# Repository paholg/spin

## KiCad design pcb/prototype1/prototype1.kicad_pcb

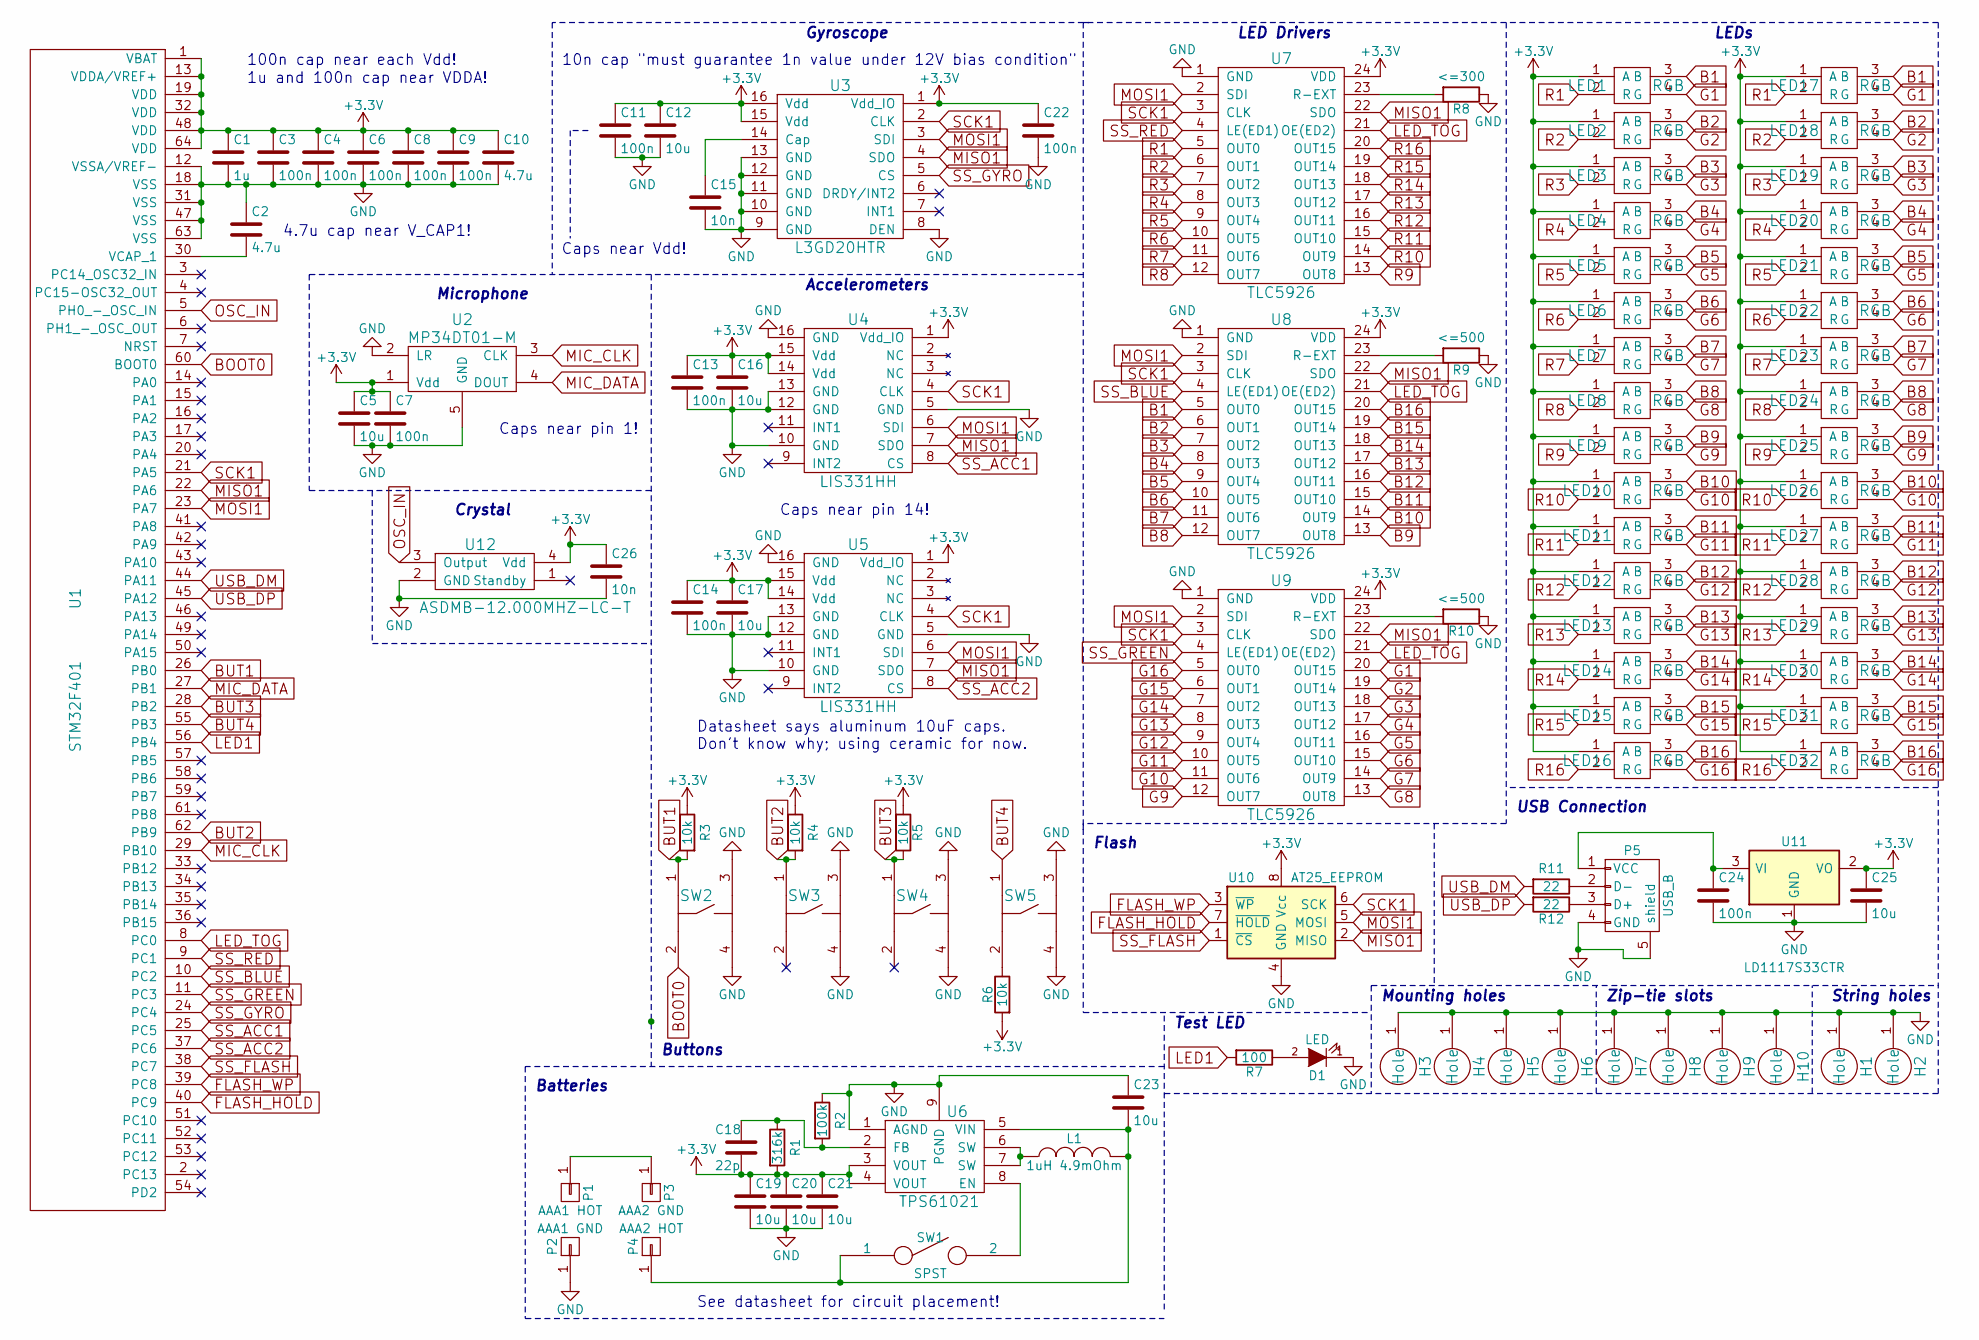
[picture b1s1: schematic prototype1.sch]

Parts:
C1: 1u; C_0805_HandSoldering
C2, C10: 4.7u; C_0603_HandSoldering
C3, C4, C6, C7, C8, C9, C11, C13, C14, C22, C24: 100n; C_0603_HandSoldering
C5, C12, C16, C17, C19, C20, C21, C23, C25: 10u; C_0805_HandSoldering
C15, C26: 10n; C_0805_HandSoldering
C18: 22p; C_0805_HandSoldering
D1: LED; LED_0603
H1, H2, H3, H4, H5, H6: Hole; Hole-3mm
H7, H8, H9, H10: Hole; Zip-tie-slot
L1: 1uH 4.9mOhm; SRU1028-10x10-Octogon
LED1, LED2, LED3, LED4, LED5, LED6, LED7, LED8, LED9, LED10, LED11, LED12, LED13, LED14, LED15, LED16, LED17, LED18, LED19, LED20, LED21, LED22, LED23, LED24, LED25, LED26, LED27, LED28, LED29, LED30, LED31, LED32: RGB; LED_CLV1L-PLCC4
P1: AAA1 HOT; test_pin
P2: AAA1 GND; test_pin
P3: AAA2 GND; test_pin
P4: AAA2 HOT; test_pin
P5: USB_B; ZX62M-B-5P
R1: 316k; R_1206_HandSoldering
R2: 100k; R_0805_HandSoldering
R3, R4, R5, R6: 10k; R_0805_HandSoldering
R7: 100; R_0805_HandSoldering
R8: <=300; Resistor_Vertical_RM5mm
R9, R10: <=500; Resistor_Vertical_RM5mm
R11, R12: 22; R_0603_HandSoldering
SW1: SPST; EVP-AYG0BA
SW2, SW3, SW4, SW5: SPST_two_terminals; Button
U1: STM32F401; TQFP-64_10x10mm_Pitch0.5mm
U2: MP34DT01-M
U3: L3GD20HTR; LGA16
U4, U5: LIS331HH; LGA16
U6: TPS61021; WSON-8_2x2mm
U7, U8, U9: TLC5926
U10: AT25_EEPROM; SOIC-8_3.9x4.9mm_Pitch1.27mm
U11: LD1117S33CTR; SOT-223
U12: ASDMB-12.000MHZ-LC-T

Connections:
+3V3: C1.1, C3.1, C4.1, C5.1, C6.1, C7.1, C8.1, C9.1, C10.1, C11.1, C12.1, C13.1, C14.1, C16.1, C17.1, C18.2, C19.1, C20.1, C21.1, C22.1, C25.1, C26.1, LED1.1 (A), LED2.1 (A), LED3.1 (A), LED4.1 (A), LED5.1 (A), LED6.1 (A), LED7.1 (A), LED8.1 (A), LED9.1 (A), LED10.1 (A), LED11.1 (A), LED12.1 (A), LED13.1 (A), LED14.1 (A), LED15.1 (A), LED16.1 (A), LED17.1 (A), LED18.1 (A), LED19.1 (A), LED20.1 (A), LED21.1 (A), LED22.1 (A), LED23.1 (A), LED24.1 (A), LED25.1 (A), LED26.1 (A), LED27.1 (A), LED28.1 (A), LED29.1 (A), LED30.1 (A), LED31.1 (A), LED32.1 (A), R1.2, R3.1, R4.1, R5.2, R6.2, U1.1 (VBAT), U1.13 (VDDA/VREF+), U1.19 (VDD), U1.32 (VDD), U1.48 (VDD), U1.64 (VDD), U2.1 (Vdd), U3.1 (Vdd_IO), U3.15 (Vdd), U3.16 (Vdd), U4.1 (Vdd_IO), U4.14 (Vdd), U4.15 (Vdd), U5.1 (Vdd_IO), U5.14 (Vdd), U5.15 (Vdd), U6.3 (VOUT), U6.4 (VOUT), U7.24 (VDD), U8.24 (VDD), U9.24 (VDD), U10.8 (Vcc), U11.2 (VO), U12.4 (Vdd)
B1: LED1.3 (B), LED17.3 (B), U8.5 (OUT0)
B2: LED2.3 (B), LED18.3 (B), U8.6 (OUT1)
B3: LED3.3 (B), LED19.3 (B), U8.7 (OUT2)
B4: LED4.3 (B), LED20.3 (B), U8.8 (OUT3)
B5: LED5.3 (B), LED21.3 (B), U8.9 (OUT4)
B6: LED6.3 (B), LED22.3 (B), U8.10 (OUT5)
B7: LED7.3 (B), LED23.3 (B), U8.11 (OUT6)
B8: LED8.3 (B), LED24.3 (B), U8.12 (OUT7)
B9: LED9.3 (B), LED25.3 (B), U8.13 (OUT8)
B10: LED10.3 (B), LED26.3 (B), U8.14 (OUT9)
B11: LED11.3 (B), LED27.3 (B), U8.15 (OUT10)
B12: LED12.3 (B), LED28.3 (B), U8.16 (OUT11)
B13: LED13.3 (B), LED29.3 (B), U8.17 (OUT12)
B14: LED14.3 (B), LED30.3 (B), U8.18 (OUT13)
B15: LED15.3 (B), LED31.3 (B), U8.19 (OUT14)
B16: LED16.3 (B), LED32.3 (B), U8.20 (OUT15)
BOOT0: SW2.2, U1.60 (BOOT0)
BUT1: R3.2, SW2.1, U1.26 (PB0)
BUT2: R4.2, SW3.1, U1.62 (PB9)
BUT3: R5.1, SW4.1, U1.28 (PB2)
BUT4: SW5.1, U1.55 (PB3)
FLASH_HOLD: U1.40 (PC9), U10.7 (~HOLD)
FLASH_WP: U1.39 (PC8), U10.3 (~WP)
G1: LED1.4 (G), LED17.4 (G), U9.20 (OUT15)
G2: LED2.4 (G), LED18.4 (G), U9.19 (OUT14)
G3: LED3.4 (G), LED19.4 (G), U9.18 (OUT13)
G4: LED4.4 (G), LED20.4 (G), U9.17 (OUT12)
G5: LED5.4 (G), LED21.4 (G), U9.16 (OUT11)
G6: LED6.4 (G), LED22.4 (G), U9.15 (OUT10)
G7: LED7.4 (G), LED23.4 (G), U9.14 (OUT9)
G8: LED8.4 (G), LED24.4 (G), U9.13 (OUT8)
G9: LED9.4 (G), LED25.4 (G), U9.12 (OUT7)
G10: LED10.4 (G), LED26.4 (G), U9.11 (OUT6)
G11: LED11.4 (G), LED27.4 (G), U9.10 (OUT5)
G12: LED12.4 (G), LED28.4 (G), U9.9 (OUT4)
G13: LED13.4 (G), LED29.4 (G), U9.8 (OUT3)
G14: LED14.4 (G), LED30.4 (G), U9.7 (OUT2)
G15: LED15.4 (G), LED31.4 (G), U9.6 (OUT1)
G16: LED16.4 (G), LED32.4 (G), U9.5 (OUT0)
GND: C1.2, C2.1, C3.2, C4.2, C5.2, C6.2, C7.2, C8.2, C9.2, C10.2, C11.2, C12.2, C13.2, C14.2, C15.2, C16.2, C17.2, C19.2, C20.2, C21.2, C22.2, C23.1, C24.2, C25.2, C26.2, D1.1 (K), H1.1, H2.1, H3.1, H4.1, H5.1, H6.1, H7.1, H8.1, H9.1, H10.1, P2.1, P5.4 (GND), P5.5 (shield), R2.1, R8.1, R9.1, R10.1, SW2.3, SW2.4, SW3.3, SW3.4, SW4.3, SW4.4, SW5.3, SW5.4, U1.12 (VSSA/VREF-), U1.18 (VSS), U1.31 (VSS), U1.47 (VSS), U1.63 (VSS), U2.2 (LR), U2.5 (GND), U3.8 (DEN), U3.9 (GND), U3.10 (GND), U3.11 (GND), U3.12 (GND), U3.13 (GND), U4.5 (GND), U4.10 (GND), U4.12 (GND), U4.13 (GND), U4.16 (GND), U5.5 (GND), U5.10 (GND), U5.12 (GND), U5.13 (GND), U5.16 (GND), U6.1 (AGND), U6.9 (PGND), U7.1 (GND), U8.1 (GND), U9.1 (GND), U10.4 (GND), U11.1 (GND), U12.2 (GND)
LED1: R7.2, U1.56 (PB4)
LED_TOG: U1.8 (PC0), U7.21 (OE(ED2)), U8.21 (OE(ED2)), U9.21 (OE(ED2))
MIC_CLK: U1.29 (PB10), U2.3 (CLK)
MIC_DATA: U1.27 (PB1), U2.4 (DOUT)
MISO1: U1.22 (PA6), U3.4 (SDO), U4.7 (SDO), U5.7 (SDO), U7.22 (SDO), U8.22 (SDO), U9.22 (SDO), U10.2 (MISO)
MOSI1: U1.23 (PA7), U3.3 (SDI), U4.6 (SDI), U5.6 (SDI), U7.2 (SDI), U8.2 (SDI), U9.2 (SDI), U10.5 (MOSI)
unnamed: C2.2, U1.30 (VCAP_1)
unnamed: C15.1, U3.14 (Cap)
unnamed: C18.1, R1.1, R2.2, U6.2 (FB)
unnamed: C23.2, L1.2, P4.1, SW1.1, U6.5 (VIN)
unnamed: C24.1, P5.1 (VCC), U11.3 (VI)
unnamed: D1.2 (A), R7.1
unnamed: L1.1, U6.6 (SW), U6.7 (SW)
unnamed: P1.1, P3.1
unnamed: P5.2 (D-), R11.1
unnamed: P5.3 (D+), R12.1
unnamed: R6.1, SW5.2
unnamed: R8.2, U7.23 (R-EXT)
unnamed: R9.2, U8.23 (R-EXT)
unnamed: R10.2, U9.23 (R-EXT)
unnamed: SW1.2, U6.8 (EN)
OSC_IN: U1.5 (PH0_-_OSC_IN), U12.3 (Output)
R1: LED1.2 (R), LED17.2 (R), U7.5 (OUT0)
R2: LED2.2 (R), LED18.2 (R), U7.6 (OUT1)
R3: LED3.2 (R), LED19.2 (R), U7.7 (OUT2)
R4: LED4.2 (R), LED20.2 (R), U7.8 (OUT3)
R5: LED5.2 (R), LED21.2 (R), U7.9 (OUT4)
R6: LED6.2 (R), LED22.2 (R), U7.10 (OUT5)
R7: LED7.2 (R), LED23.2 (R), U7.11 (OUT6)
R8: LED8.2 (R), LED24.2 (R), U7.12 (OUT7)
R9: LED9.2 (R), LED25.2 (R), U7.13 (OUT8)
R10: LED10.2 (R), LED26.2 (R), U7.14 (OUT9)
R11: LED11.2 (R), LED27.2 (R), U7.15 (OUT10)
R12: LED12.2 (R), LED28.2 (R), U7.16 (OUT11)
R13: LED13.2 (R), LED29.2 (R), U7.17 (OUT12)
R14: LED14.2 (R), LED30.2 (R), U7.18 (OUT13)
R15: LED15.2 (R), LED31.2 (R), U7.19 (OUT14)
R16: LED16.2 (R), LED32.2 (R), U7.20 (OUT15)
SCK1: U1.21 (PA5), U3.2 (CLK), U4.4 (CLK), U5.4 (CLK), U7.3 (CLK), U8.3 (CLK), U9.3 (CLK), U10.6 (SCK)
SS_ACC1: U1.25 (PC5), U4.8 (CS)
SS_ACC2: U1.37 (PC6), U5.8 (CS)
SS_BLUE: U1.10 (PC2), U8.4 (LE(ED1))
SS_FLASH: U1.38 (PC7), U10.1 (~CS)
SS_GREEN: U1.11 (PC3), U9.4 (LE(ED1))
SS_GYRO: U1.24 (PC4), U3.5 (CS)
SS_RED: U1.9 (PC1), U7.4 (LE(ED1))
USB_DM: R11.2, U1.44 (PA11)
USB_DP: R12.2, U1.45 (PA12)

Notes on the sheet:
4.7u cap near V_CAP1!
Caps near Vdd!
See datasheet for circuit placement!
100n cap near each Vdd!
Caps near pin 14!
10n cap "must guarantee 1n value under 12V bias condition"
Datasheet says aluminum 10uF caps. Don't know why; using ceramic for now.
1u and 100n cap near VDDA!
LED Drivers
LEDs
Gyroscope
Accelerometers
USB Connection
Flash
Test LED
Buttons
Batteries
Microphone
Caps near pin 1!
Crystal
String holes
Mounting holes
Zip-tie slots

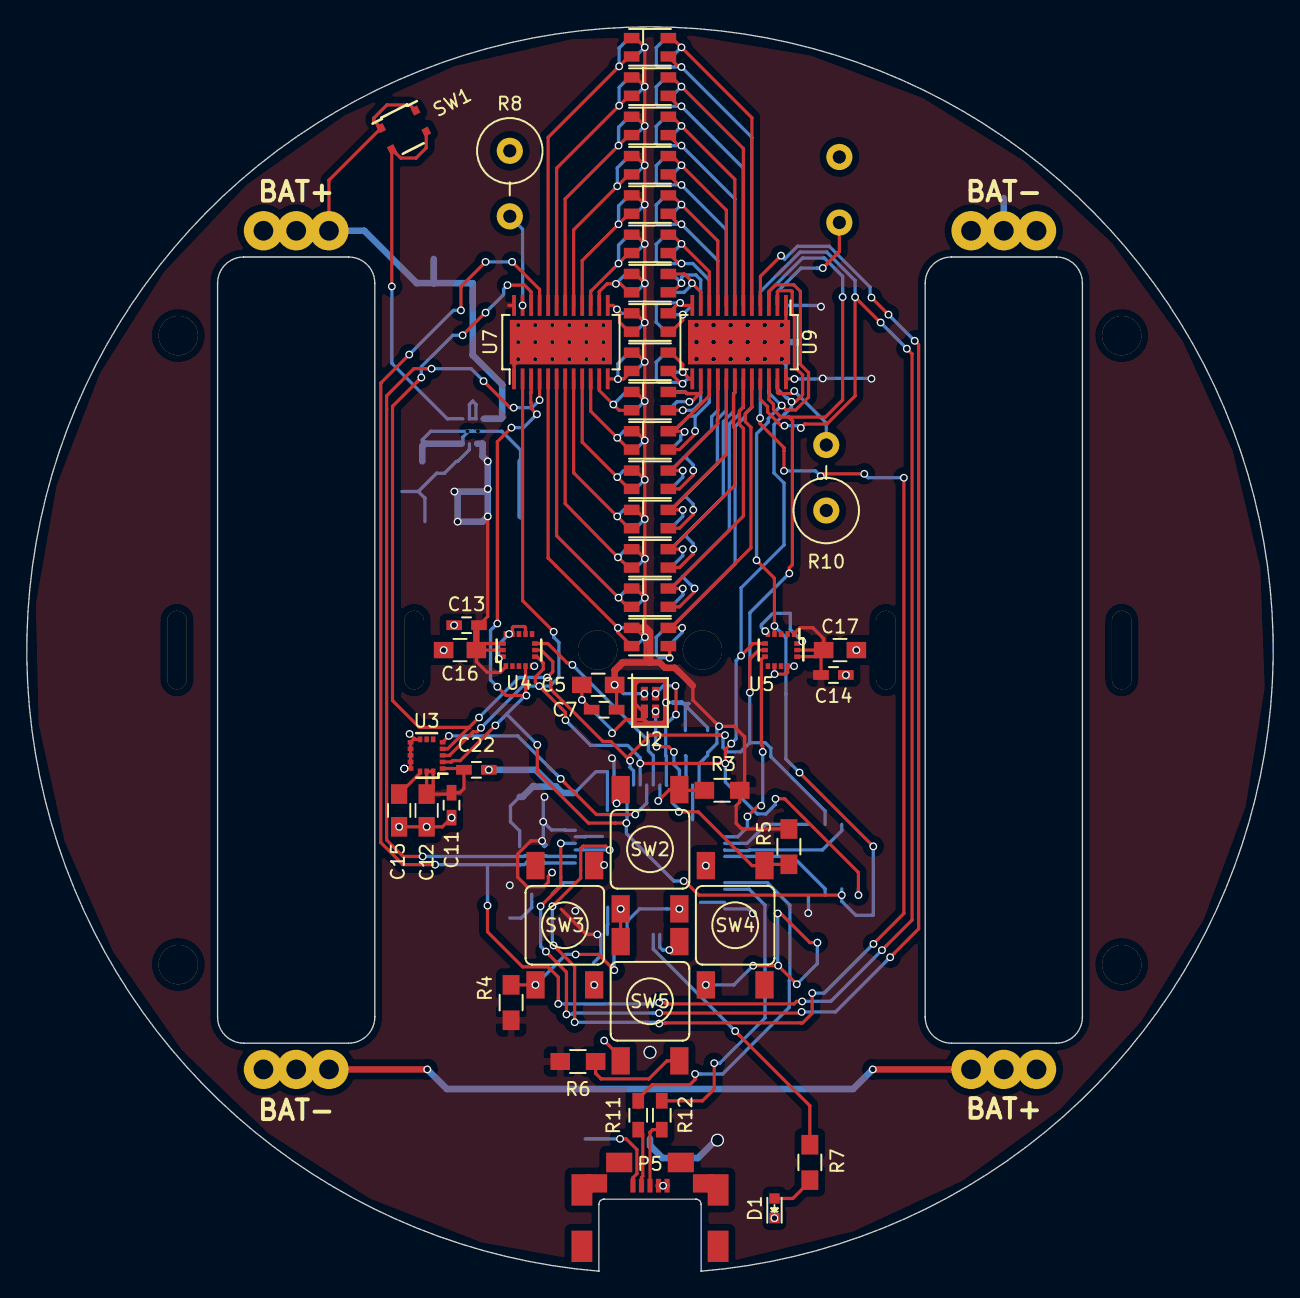
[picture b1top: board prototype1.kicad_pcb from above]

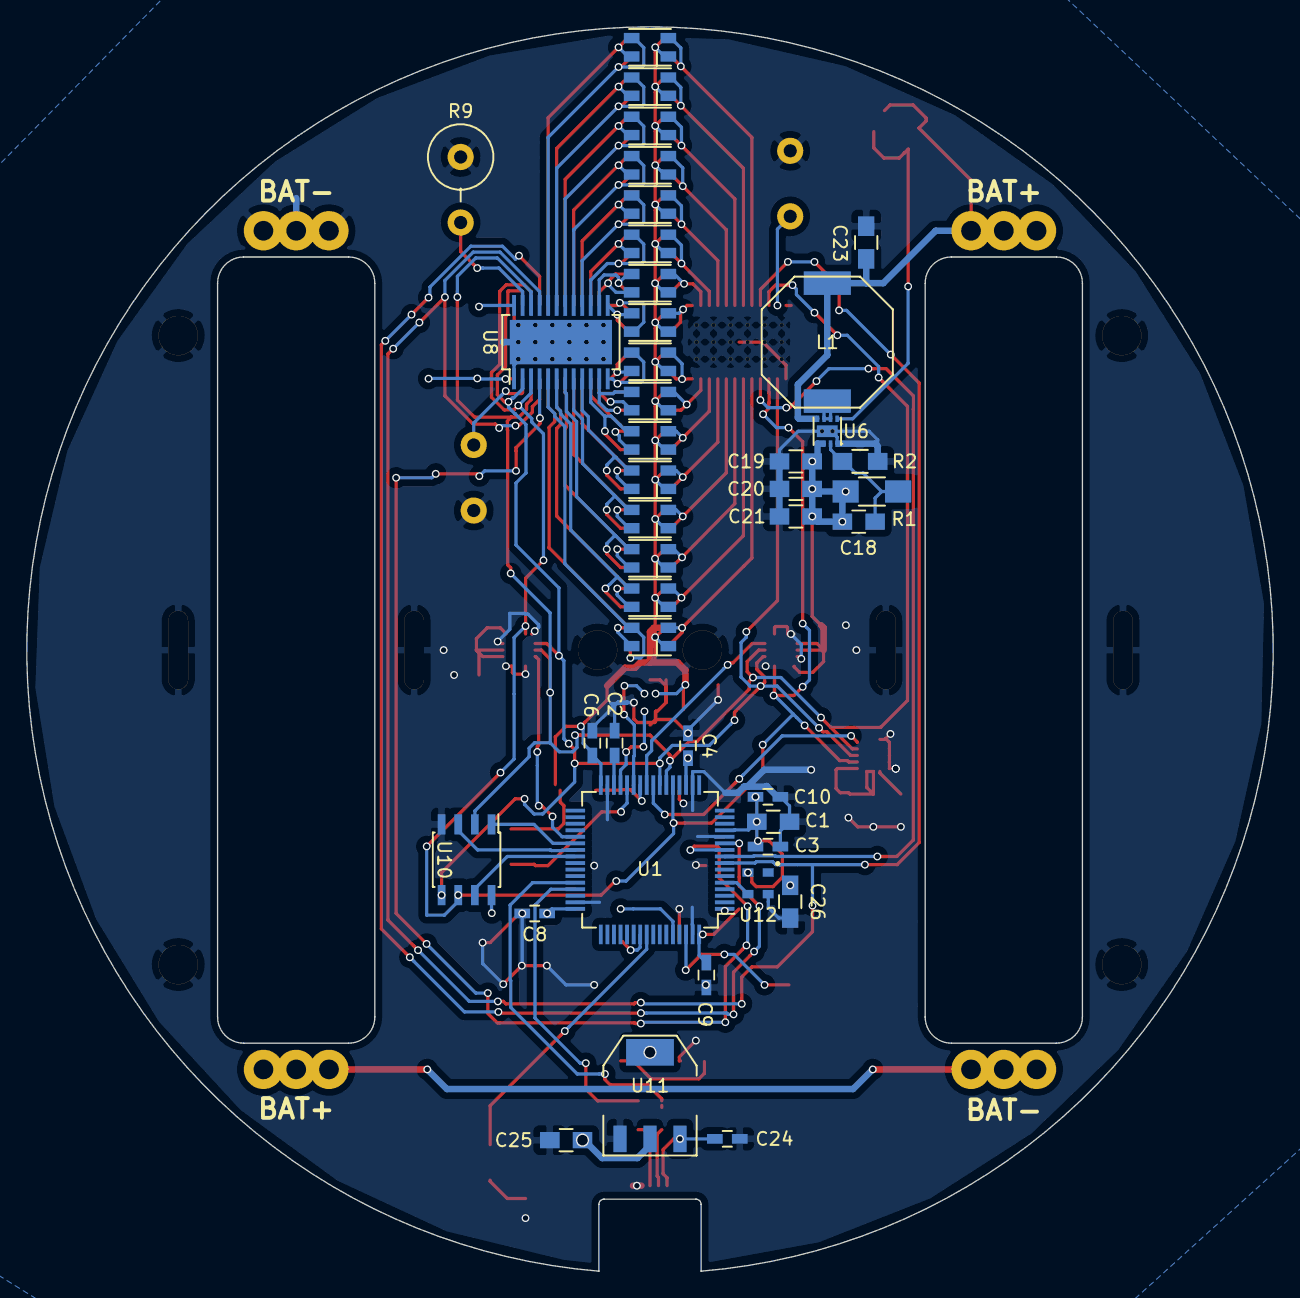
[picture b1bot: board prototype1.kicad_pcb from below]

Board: 2 copper layers, 95.1 x 95.0 mm, 104 parts (42 on the bottom side), 89 nets.

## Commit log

2016-06-11 fix custom kicad libs
2016-06-11 minor cleanup
2016-06-11 export prototype to cad
2016-06-12 Working on pcb
2016-06-12 More pcb changes
2016-06-14 More pcb stuff
2016-06-26 pcb schematic almost done!
2016-06-26 Switch to stm32f401
2016-07-12 Schematic mostly done
2016-07-12 Add footprint
2016-07-12 Working on schematic
2016-07-13 Workin on pcb!
2016-07-14 pcb stuff
2016-07-16 Maybe changed something?
2016-07-17 Change pcb layout a bit
2016-07-17 Connected many things on pcb
2016-07-17 swap a couple pins on stm32
2016-07-17 pcb is connected!
2016-07-20 Finish prototype1!!!
2016-07-20 make spin sim work much better
2016-07-20 spinulation tweaks
2016-07-21 Some cleanup / restructuring of spinulation
2016-07-21 forgot a file
2016-07-21 spinulation changes
2016-07-21 Fix spinulator aspect ratio
2016-07-21 remove cad files
2016-07-21 remove csrc stuff
2016-07-21 remove last file from csrc
2016-07-21 Playing with color. Renamed an example
2016-07-21 Fix cargo.toml
2016-07-21 rename another example
2016-07-21 forgot to add
2016-07-22 remove dependency on std::thread::sleep
2016-07-22 fix (temporarily) rand dependency for no_std
2016-07-22 make sim default
2016-07-22 Make things, esp ArrayLength stuff, better
2016-07-22 add example cycle2
2016-07-22 make GradientSlice and impl Deref for Gradient
2016-07-22 cleanup
2016-07-22 minor nicety
2016-07-22 some example tweaking
2016-07-22 fix exiting
2016-07-22 minor tweaks
2016-07-22 fix bug where thing could get stuck at top speed
2016-07-22 fix it really
2016-07-23 minor example tweak
2016-07-23 Move rust stuff to root dir
2016-07-23 Add image display API
2016-07-23 Add rudimentary image conversion
2016-07-23 impl Index for LedMatrixSlice
2016-07-23 some tweaks
2016-07-23 fix bug in convert script
2016-07-24 Some restructuring
2016-07-27 Image stuff moved out, started getting compiling to arm setup
